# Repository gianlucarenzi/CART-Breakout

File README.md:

# CART-Breakout
=====================================

BreakOut Board for CART Bus Connector Atari 130XE

This is a simple cartridge breakout board, useful for many purposes developing hardware for Atari 8-bit line of computers

# Rendered Images
# 
# 
# 

Hardware License
---------------------------
Copyright (C) 2018/2019 Gianluca Renzi <gianlucarenzi@eurek.it> <icjtqr@gmail.com>

The hardware of this project is released as free/open hardware under the
GNU GPL v3 License terms. See licence.txt for details.

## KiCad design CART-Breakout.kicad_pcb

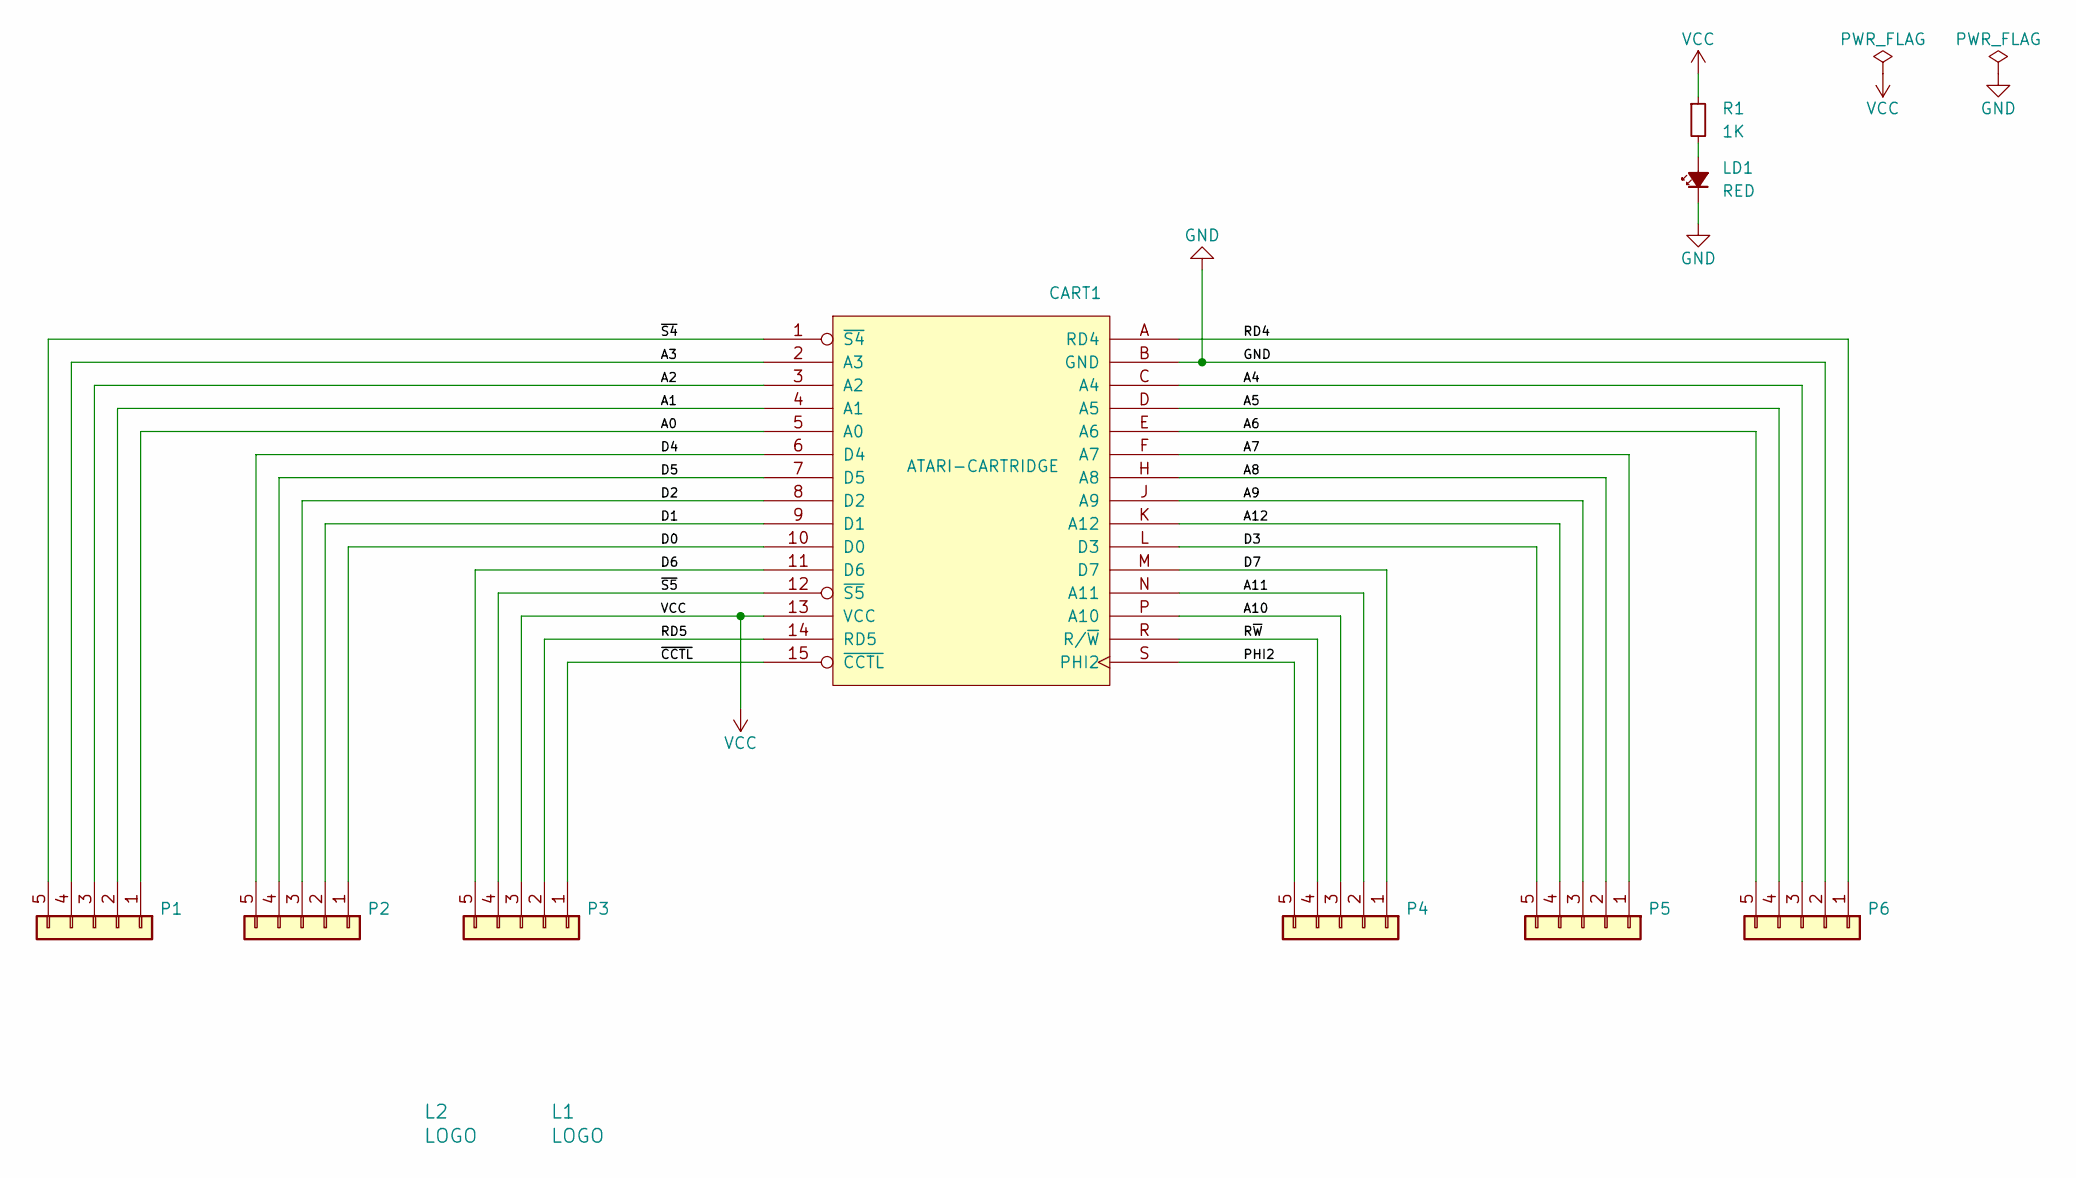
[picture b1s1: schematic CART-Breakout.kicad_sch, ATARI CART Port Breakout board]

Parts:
CART1: ATARI-CARTRIDGE; ATARI-LEFT-CARTRIDGE
L1: LOGO; OSHW-Logo2_7.3x6mm_SilkScreen
L2: LOGO; KiCad-Logo2_5mm_SilkScreen
LD1: RED; LED_1206_3216Metric_Pad1.42x1.75mm_HandSolder; LCSC C965822
P1, P2, P3, P4, P5, P6: Conn_01x05; PinHeader_1x05_P2.54mm_Vertical
R1: 1K; R_0805_2012Metric_Pad1.20x1.40mm_HandSolder; LCSC C17513

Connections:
/A0: CART1.5 (A0), P1.1
/A1: CART1.4 (A1), P1.2
/A2: CART1.3 (A2), P1.3
/A3: CART1.2 (A3), P1.4
/A4: CART1.C (A4), P6.3
/A5: CART1.D (A5), P6.4
/A6: CART1.E (A6), P6.5
/A7: CART1.F (A7), P5.1
/A8: CART1.H (A8), P5.2
/A9: CART1.J (A9), P5.3
/A10: CART1.P (A10), P4.3
/A11: CART1.N (A11), P4.2
/A12: CART1.K (A12), P5.4
/D0: CART1.10 (D0), P2.1
/D1: CART1.9 (D1), P2.2
/D2: CART1.8 (D2), P2.3
/D3: CART1.L (D3), P5.5
/D4: CART1.6 (D4), P2.5
/D5: CART1.7 (D5), P2.4
/D6: CART1.11 (D6), P3.5
/D7: CART1.M (D7), P4.1
/PHI2: CART1.S (PHI2), P4.5
/RD4: CART1.A (RD4), P6.1
/RD5: CART1.14 (RD5), P3.2
/R~W: CART1.R (R/~W), P4.4
/~CCTL: CART1.15 (~CCTL), P3.1
/~S4: CART1.1 (~S4), P1.5
/~S5: CART1.12 (~S5), P3.4
GND: CART1.B (GND), LD1.1 (K), P6.2
unnamed: LD1.2 (A), R1.2
VCC: CART1.13 (VCC), P3.3, R1.1

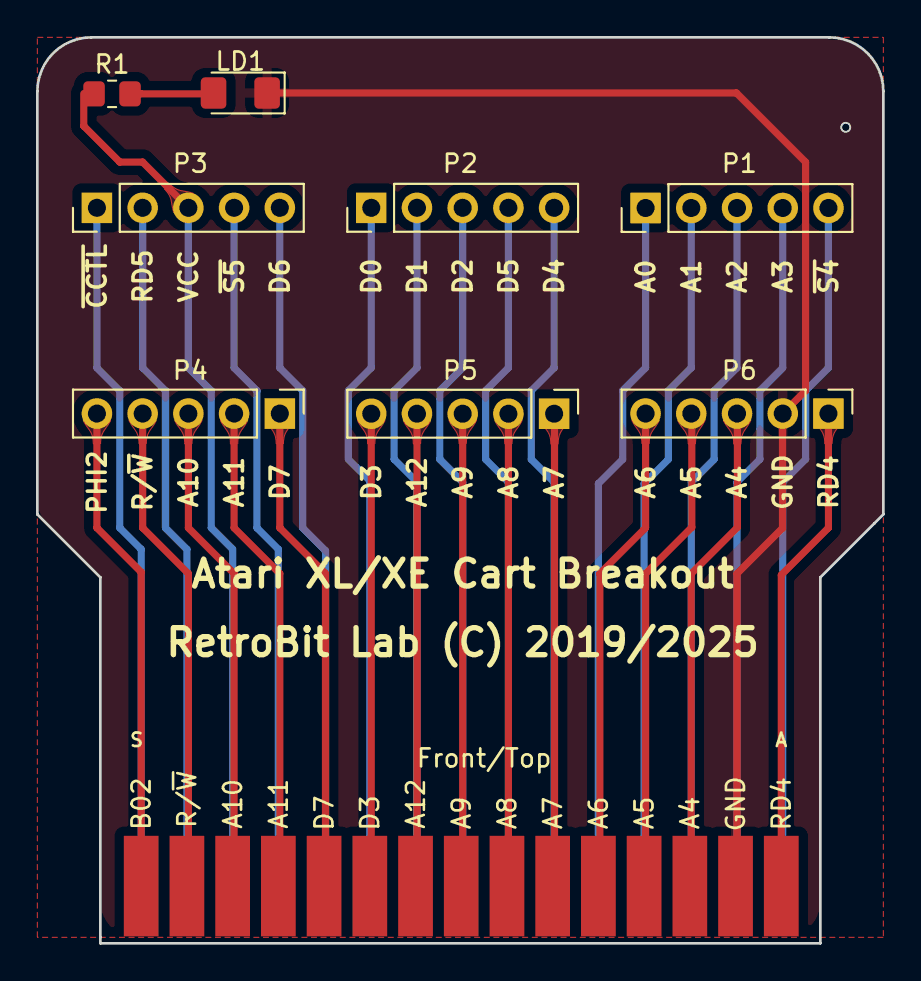
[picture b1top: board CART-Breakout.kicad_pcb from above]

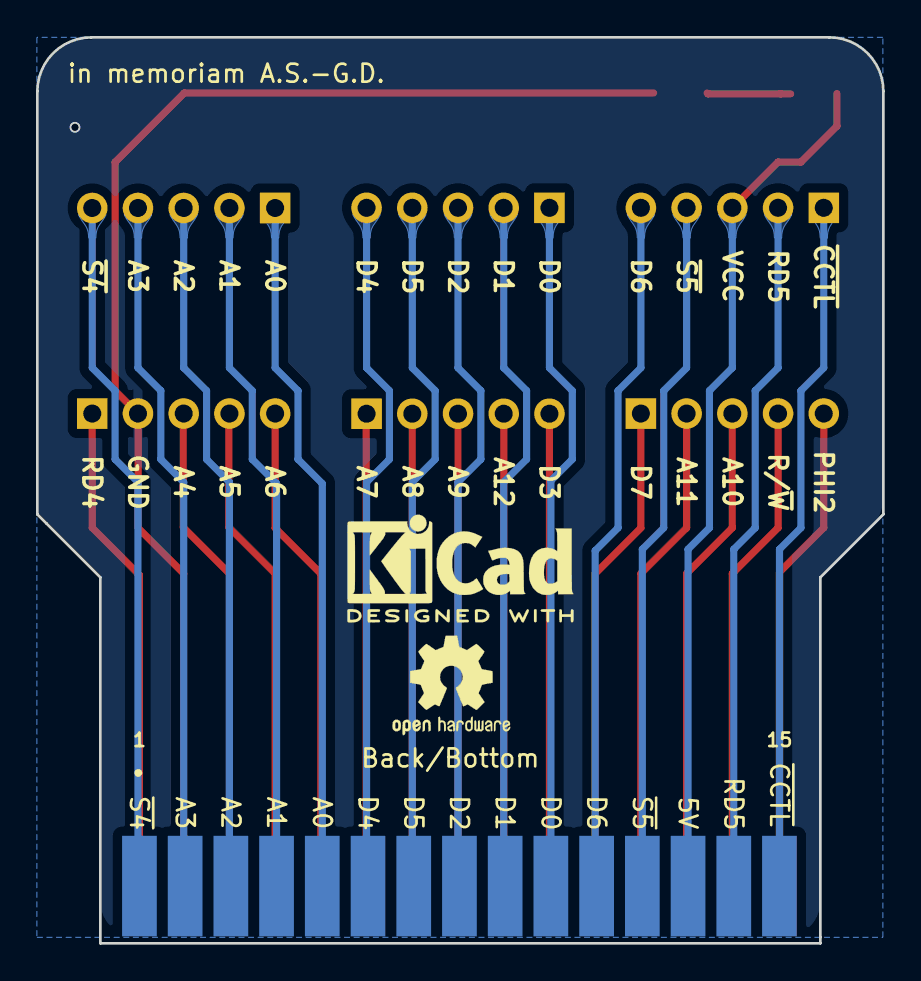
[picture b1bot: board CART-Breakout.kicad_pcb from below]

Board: 2 copper layers, 47.0 x 50.3 mm, 11 parts (2 on the bottom side), 31 nets.

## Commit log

2019-04-14 First import
2019-04-14 Added license
2019-04-14 Added images
2019-04-14 added blank spaces
2019-06-07 Added for PCB production JLCPCB 2019-06-07
2025-07-24 Removed
2025-07-24 Updated from KiCAD 4 to KiCAD 5.1.19
2025-07-24 Interactive BOM created
2025-07-24 Gerbers created with KiCAD 5
2025-10-09 Migrate to KiCAD 9+
2025-10-10 Updated for KiCAD 9
2025-10-10 Added. Generated by KiCAD 9
2025-10-10 Updated after KiCAD9 upgrade
2025-11-01 RetroBitLab library

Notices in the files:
CART-Breakout.kicad_pcb:
RetroBit Lab (C) 2019/2025
